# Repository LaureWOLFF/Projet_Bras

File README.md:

# 🦾 Robot Control via Electromyographic (EMG) Signals

Ce projet, réalisé dans le cadre de la deuxième année d'ingénieur à l'**ENSEA (Cergy)**, porte sur la conception et la réalisation d'un capteur électromyographique (EMG) complet et l'activation d'un robot par ces signaux. L'objectif est de capturer l'activité électrique des muscles du bras pour permettre, à terme, le contrôle du robot.

## 📌 Présentation du Projet
Le système permet de détecter les signaux bioélectriques de très faible amplitudes émis lors d'une contraction musculaire, de les traiter analogiquement pour les rendre exploitables, puis de les numériser via un microcontrôleur **ESP32**.

### 🛠 Caractéristiques
* **Cible :** Muscles du bras (biceps et ceux de l'avant-bras).
* **Signal d'entrée :** Amplitude de $10\mu\text{V}$ à $5\text{mV}$, fréquence de 10 Hz à 500 Hz.
* **Traitement Analogique :** * Amplification d'instrumentation (Gain élevé).
    * Filtrage passe-bande (élimination du bruit 50 Hz et des hautes fréquences).
    * Redressement et lissage du signal (enveloppe du signal).
* **Numérisation :** ADC de l'ESP32 (échantillonnage et traitement logiciel).

---

## 🏗 Architecture du capteur EMG

Le projet est actuellement divisé en plusieurs blocs:

1.  **Étage de Pré-amplification :** Utilisation d'un amplificateur d'instrumentation pour extraire le signal différentiel des électrodes.
2.  **Filtrage Actif :** Nettoyage du signal pour ne garder que la bande utile de l'EMG.
3.  **Redresseur de précision :** Conversion du signal alternatif en signal continu (enveloppe de contraction).
4.  **Adaptation de tension :** Ajustement du signal vers une plage 0-3.3V compatible avec l'ESP32.

---
## 🤖 Cahine d'information Capteur --> Robot

Pour piloter le robot, l'information circule à travers les étapes suivantes :

1. **Acquisition :** Captation des micro-tensions sur la peau via les électrodes.
2. **Traitement Analogique :** Traitement via le capteur EMG.
3. **Numérisation :** L'ESP32 convertit le signal analogique en données numériques via son ADC.
4. **Interprétation :** Analyse du seuil de tension pour détecter une contraction ou un relâchement.
5. **Communication :** Envoi des commandes via Bluetooth/Wi-Fi vers le système de contrôle du robot.
6. **Actionnement  :** Le robot exécute le mouvement correspondant (ex: fermeture de la pince).

---
## 🚀 État d'avancement à la mi-parcours (S7)

* ✅ **Étude théorique :** Analyse des signaux EMG et définition des besoins d'amplification.
* ✅ **Choix des composants :** Passage sur des AOP type TL08x pour la réalisation physique.
* ✅ **Conception d'un prototype:** Saisie de schéma et assignation des empreintes (SOIC-8 / 0805) sur KiCad pour soudure au four.
* 🔲 **Poursuite du projet :** Finition du prototype, réalisation du PCB, tests réels avec électrodes et développement du code de traitement sur l'ESP32 (filtres numériques, Bluetooth/Wi-Fi).

---

## 📋 Travail effectué lors du S8
* **Simulation complète du captuer EMG**: Pour palier aux dysfonctionnement du prototype, on a simuler entierment le composant jusqu'à avoir le comportment voulu.
* **Réalisation du PCB**: le capteur et une carte de commande pour assebler tous les éléments
* **Travail informatique**: écriture de code afin de faire bouger le robot en fonction des mouvement (ouverture de la main, contration du muscle).
  
---

## 🔝Evolution de ce projet et axes de développement

---

## 📦 Technologies utilisées
* **CAO Électronique :** LTspice, Niryo, KiCad 9.0.
* **Matériel :** ESP32, MyoWear, composants actifs (AOP TL081) et passifs.
* **Langages :** C (Arduino IDE / PlatformIO), ROS\ROS2, Python.

---

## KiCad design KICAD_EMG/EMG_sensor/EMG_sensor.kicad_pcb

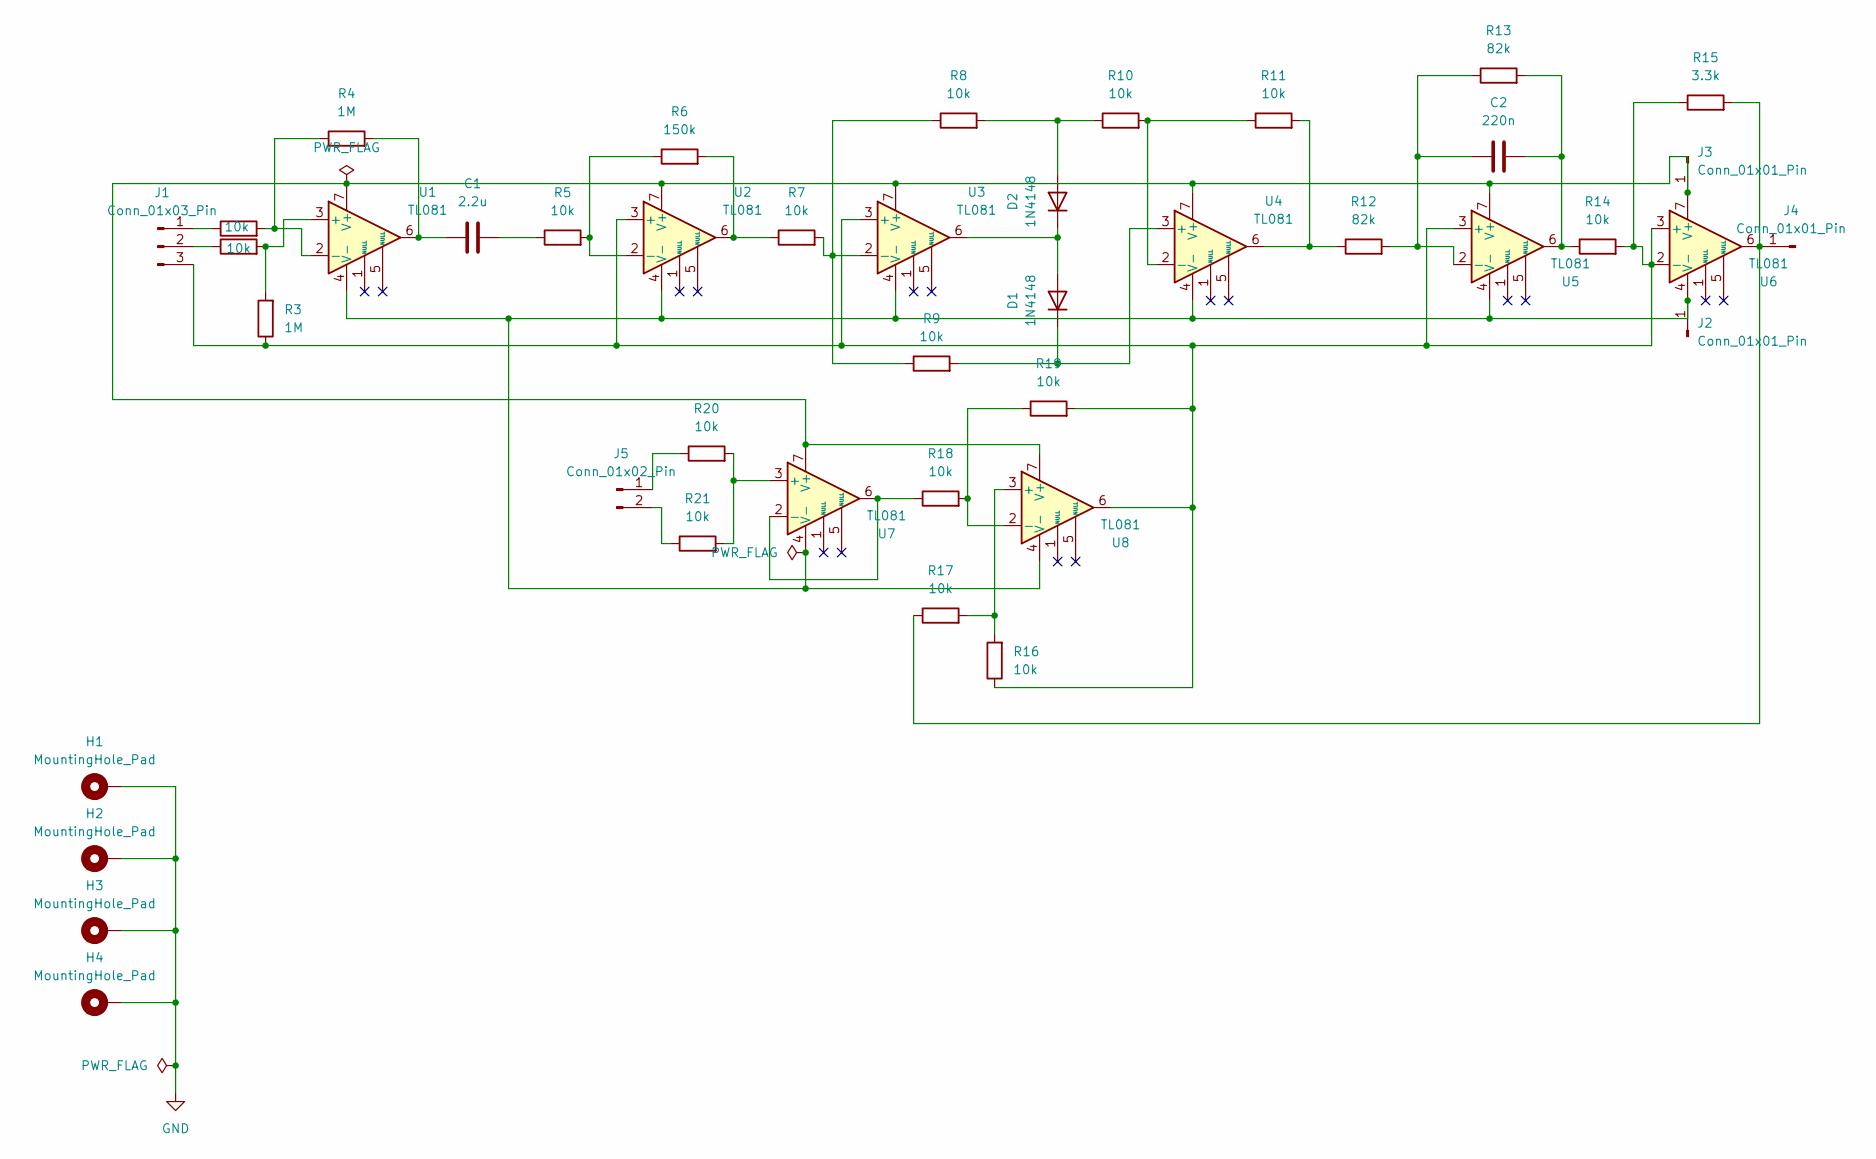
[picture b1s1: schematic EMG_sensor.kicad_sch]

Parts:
C1: 2.2u; C_0402_1005Metric_Pad0.74x0.62mm_HandSolder
C2: 220n; C_0402_1005Metric_Pad0.74x0.62mm_HandSolder
D1, D2: 1N4148; D_SOD-123
H1, H2, H3, H4: MountingHole_Pad; MountingHole_2.2mm_M2_Pad
J1: Conn_01x03_Pin; FanPinHeader_1x03_P2.54mm_Vertical
J2, J3, J4: Conn_01x01_Pin; PinHeader_1x01_P2.54mm_Vertical
J5: Conn_01x02_Pin; JST_EH_B2B-EH-A_1x02_P2.50mm_Vertical
R1, R2, R5, R7, R8, R9, R10, R11, R14, R16, R17, R18, R19, R20, R21: 10k; R_0402_1005Metric_Pad0.72x0.64mm_HandSolder
R3, R4: 1M; R_0402_1005Metric_Pad0.72x0.64mm_HandSolder
R6: 150k; R_0402_1005Metric_Pad0.72x0.64mm_HandSolder
R12, R13: 82k; R_0402_1005Metric_Pad0.72x0.64mm_HandSolder
R15: 3.3k; R_0402_1005Metric_Pad0.72x0.64mm_HandSolder
U1, U2, U3, U4, U5, U6, U7, U8: TL081; SO-8_3.9x4.9mm_P1.27mm

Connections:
GND: H1.1, H2.1, H3.1, H4.1
unnamed: C1.1, R4.2, U1.6
unnamed: C1.2, R5.1
unnamed: C2.1, R13.2, R14.1, U5.6
unnamed: D1.2 (A), D2.1 (K), U3.6
unnamed: D1.1 (K), R9.2, U4.3 (+)
unnamed: D2.2 (A), R8.2, R10.1
unnamed: J1.1, R1.1
unnamed: J1.2, R2.1
unnamed: J1.3, R3.1, R14.2, R15.1, R16.1, R19.2, U2.3 (+), U3.3 (+), U5.3 (+), U6.2 (-), U6.3 (+), U8.6
unnamed: J2.1, U1.4 (V-), U2.4 (V-), U3.4 (V-), U4.4 (V-), U5.4 (V-), U6.4 (V-), U7.4 (V-), U8.4 (V-)
unnamed: J3.1, U1.7 (V+), U2.7 (V+), U3.7 (V+), U4.7 (V+), U5.7 (V+), U6.7 (V+), U7.7 (V+), U8.7 (V+)
unnamed: J4.1, R15.2, R17.1, U6.6
unnamed: J5.1, R20.1
unnamed: J5.2, R21.1
unnamed: R6.2, R7.1, U2.6
unnamed: R11.2, R12.1, U4.6
unnamed: R2.2, R3.2, U1.3 (+)
unnamed: R1.2, R4.1, U1.2 (-)
unnamed: R5.2, R6.1, U2.2 (-)
unnamed: R7.2, R8.1, R9.1, U3.2 (-)
unnamed: R10.2, R11.1, U4.2 (-)
unnamed: C2.2, R12.2, R13.1, U5.2 (-)
unnamed: R20.2, R21.2, U7.3 (+)
unnamed: R18.1, U7.2 (-), U7.6
unnamed: R16.2, R17.2, U8.3 (+)
unnamed: R18.2, R19.1, U8.2 (-)

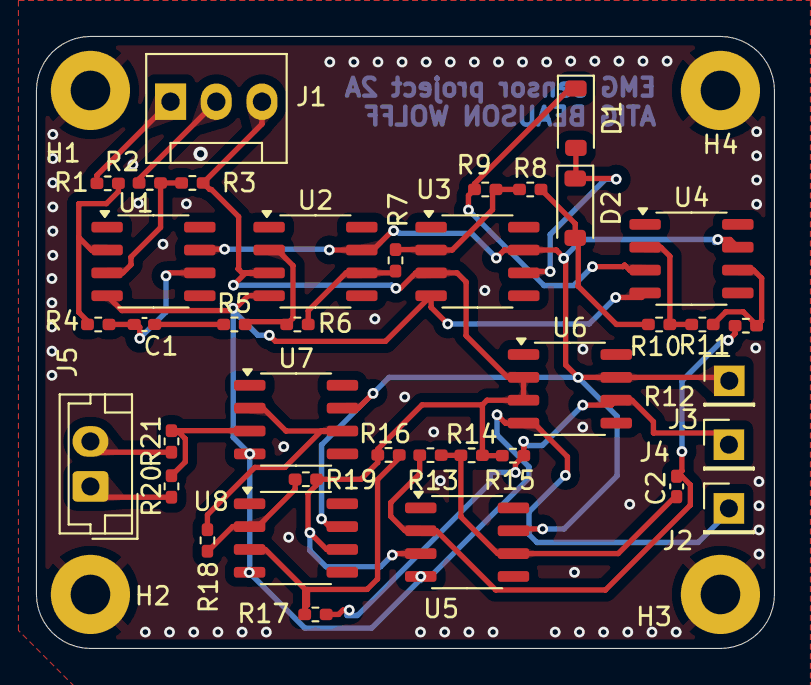
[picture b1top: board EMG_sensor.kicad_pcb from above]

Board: 2 copper layers, 41.0 x 34.0 mm, 42 parts (0 on the bottom side), 27 nets.

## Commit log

2026-02-10 Add simple connection test script for robot control
2026-02-10 Add TCP server for ESP32 MOVE signal handling
2026-02-10 Add ESP32 code for WiFi connection and voltage monitoring
    This code connects an ESP32 to a WiFi network, reads an analog voltage from a specified pin, and sends a command to a server when the voltage exceeds a threshold.
2026-03-02 Ajout denombreux fichiers dont la première ver. du PCB
2026-03-10 le PCB avec les piste à 0.3 et 0 erreur
2026-03-17 PCB modifié et envoyé en ticket
2026-03-24 Add files via upload
    code de décision ouverture/fermeture avec seuils de L'ESP 32.
2026-03-24 Implement gripper server for Niryo robot control
2026-03-31 Update esp_server
